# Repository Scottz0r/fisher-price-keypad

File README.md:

# Fisher Price Keypad

Turning a Fisher Price Smart Stages keypad into a HID Keyboard.

## Wut?

I really wanted to turn a Fisher Price tablet into a keyboard that works over USB for the kicks and giggles.

This turned into a multi-part project where I learned PCB design (with KiCad) as a drop-in replacement to the factory board in the tablet.

The software is made with the Arduino framework to make things easy. The `Keyboard.h` header makes it simple to turn a microcontroller into a HID Keyboard.

## Hardware

* Fisher Price "Smart Stages" Tablet
* Custom PCBs (to replace tablet's PCB)
* Adafruit ItsyBitsy (or any Arduino that can use `Keyboard.h`)

## Custom PCB

I created a custom PCB to replace the board that comes with the tablet. This custom board allows pins or connectors to be soldered so the keypad can be used with an Arduino.

The PCB can be printed with the gerbers in [the gerber zip](fp_tablet_keypad_v1_gerbers.zip). I printed my boards through [OSHPark](https://oshpark.com/). It cost about $9.00 (USD) to print 3 boards.

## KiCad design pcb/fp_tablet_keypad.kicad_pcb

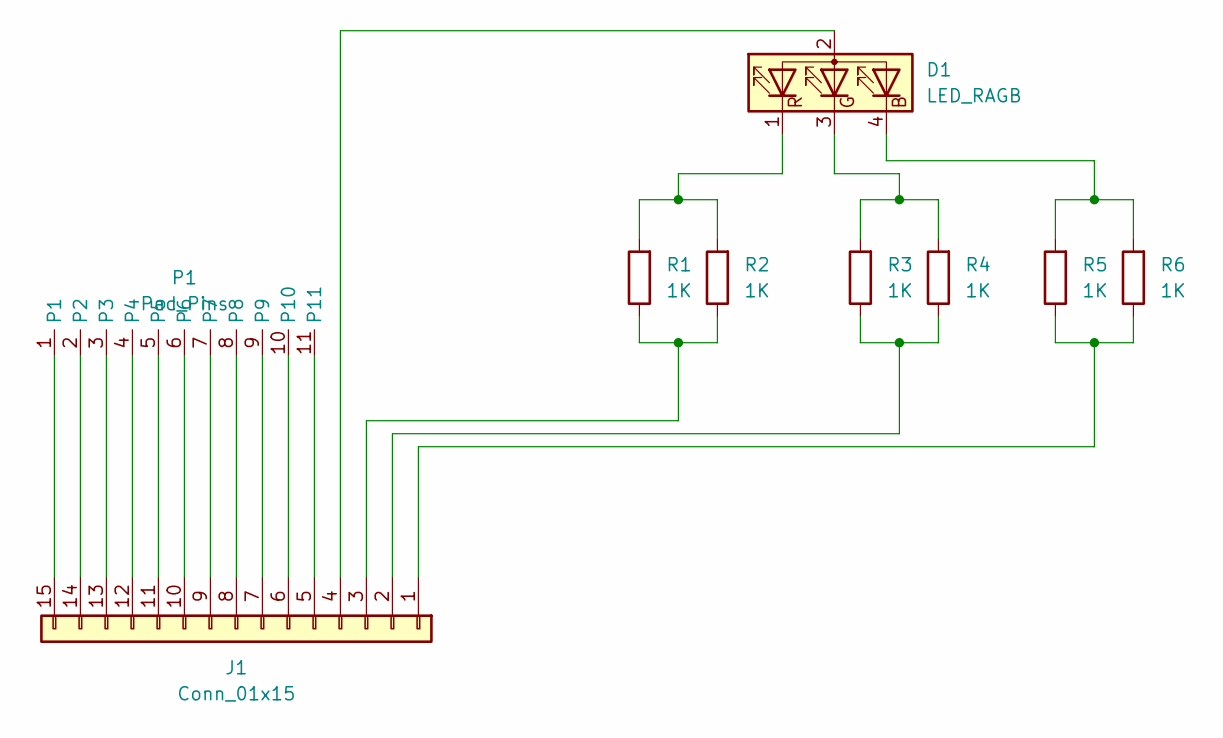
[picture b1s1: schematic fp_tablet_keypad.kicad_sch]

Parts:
D1: LED_RAGB; LED_D5.0mm-4_RGB_Wide_Pins
J1: Conn_01x15; PinHeader_1x15_P2.54mm_Vertical
P1: Pad_Pins; Keypad Pads
R1, R2, R3, R4, R5, R6: 1K; R_1206_3216Metric

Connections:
unnamed: D1.1 (RK), R1.2, R2.2
unnamed: D1.2 (A), J1.4
unnamed: D1.3 (GK), R3.2, R4.2
unnamed: D1.4 (BK), R5.2, R6.2
unnamed: J1.1, R5.1, R6.1
unnamed: J1.2, R3.1, R4.1
unnamed: J1.3, R1.1, R2.1
unnamed: J1.5, P1.11
unnamed: J1.6, P1.10
unnamed: J1.7, P1.9
unnamed: J1.8, P1.8
unnamed: J1.9, P1.7
unnamed: J1.10, P1.6
unnamed: J1.11, P1.5
unnamed: J1.12, P1.4
unnamed: J1.13, P1.3
unnamed: J1.14, P1.2
unnamed: J1.15, P1.1

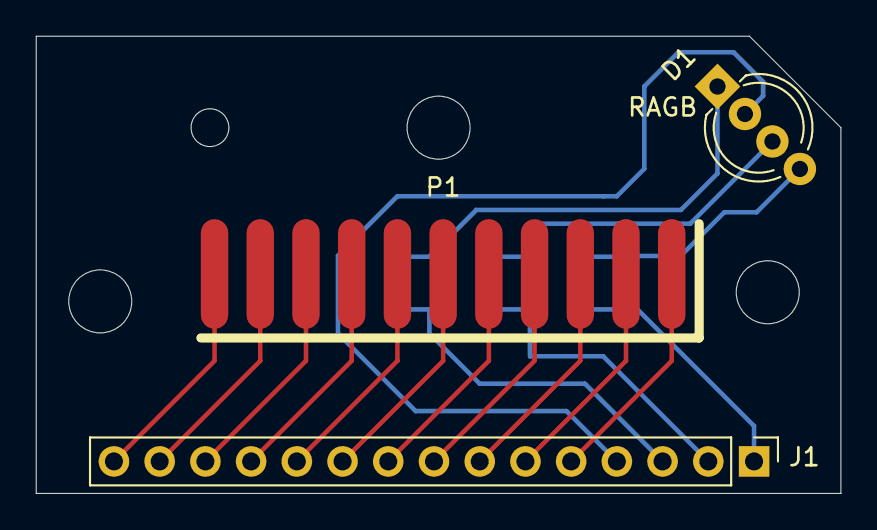
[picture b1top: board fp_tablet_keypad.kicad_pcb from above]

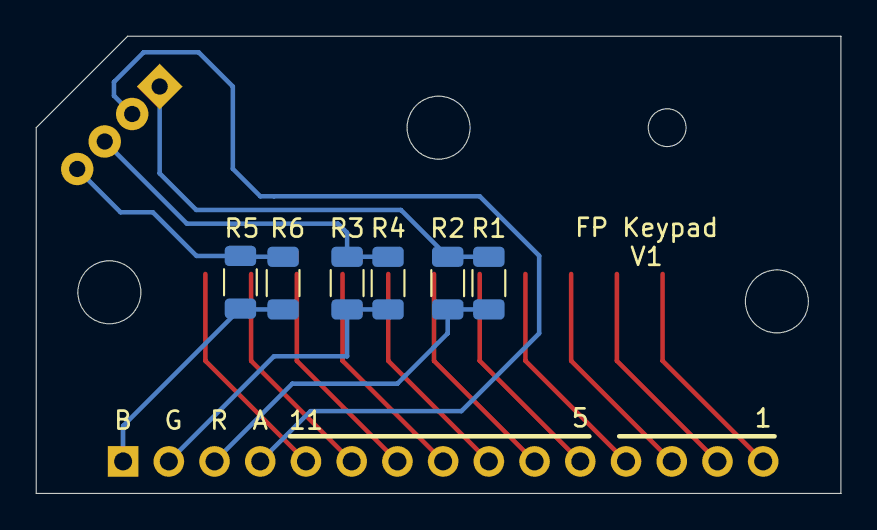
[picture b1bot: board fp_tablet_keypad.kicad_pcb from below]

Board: 2 copper layers, 44.7 x 25.4 mm, 9 parts (6 on the bottom side), 18 nets.

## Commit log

2022-01-19 Added initial files
    Adding files to project. This is a simple "v1" that works as a keypad, but without a LED.
2022-01-22 Added initial files for lighting RGB LED with keypress.
2022-01-22 Fixes and support for all LED colors
